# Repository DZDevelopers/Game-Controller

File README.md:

# Game Controller

This is a game controller powered by an Arduino Nano RP2040. It features two joysticks and ten buttons, designed for custom gaming and input projects.

This project is fully open-source and includes schematics, PCB design, and a simple enclosure.
### Overall game controller

### Schematic

### PCB

## Hardware Overview

Microcontroller: Arduino Micro RP2040

Buttons: Push Button Switch

joysticks: COM-09032

## Bill of Materials (BOM)

1 x Raspberry Pi Pico

10 x Push Button Switch

2 x COM-09032

1 × Custom-designed PCB

1 × Case (3D-printed)

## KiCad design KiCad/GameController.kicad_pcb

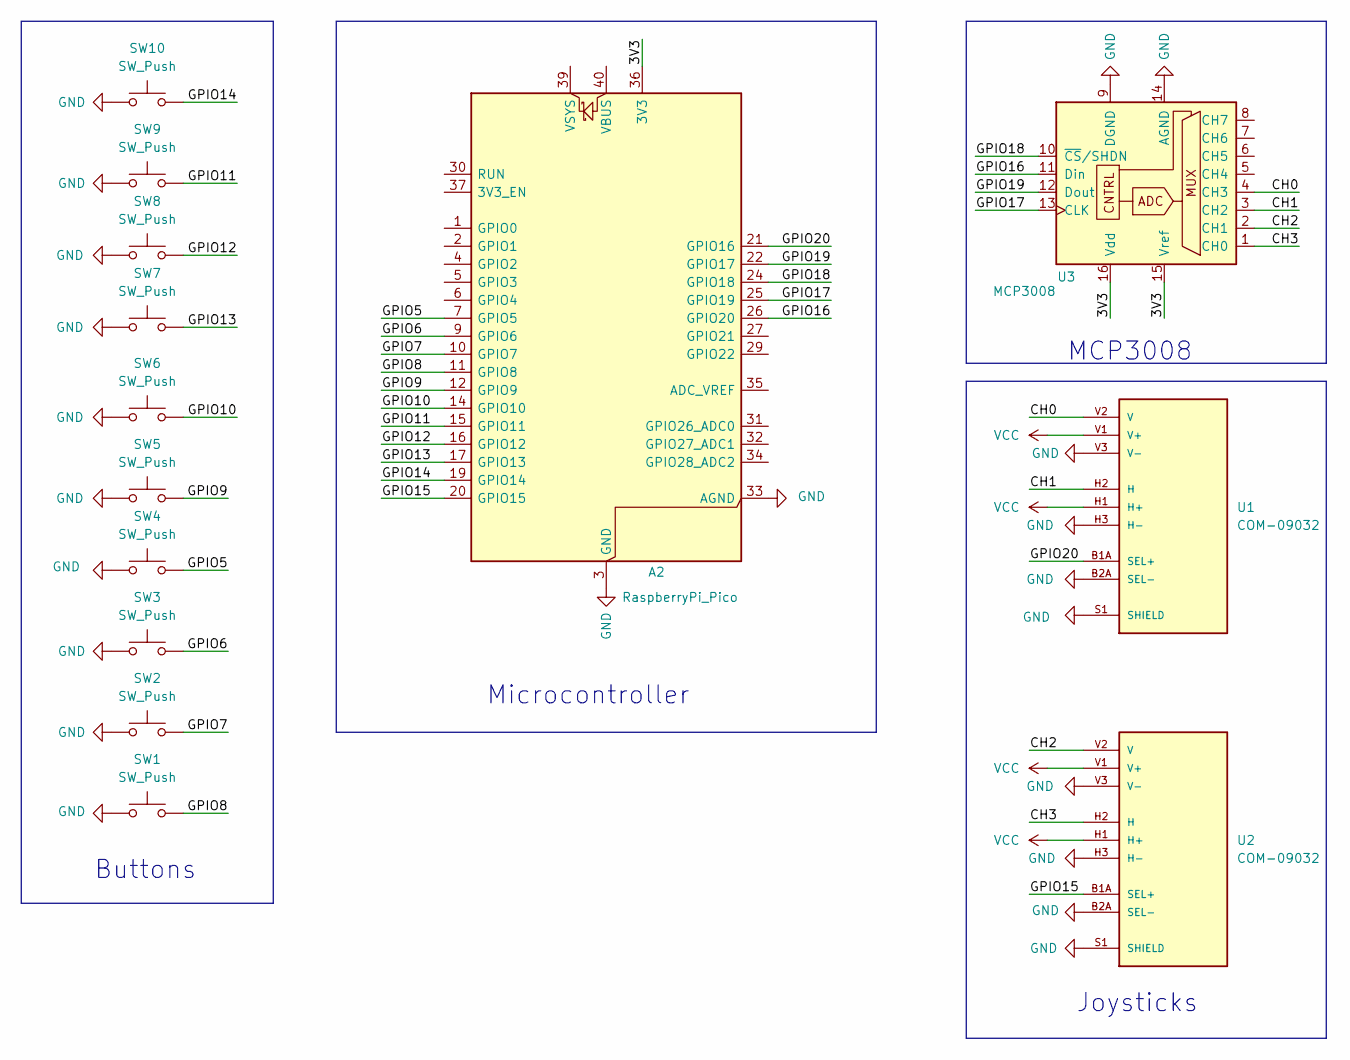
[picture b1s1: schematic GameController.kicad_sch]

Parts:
A2: RaspberryPi_Pico; RaspberryPi_Pico_Common_THT
SW1, SW2, SW3, SW4, SW5, SW6, SW7, SW8, SW9, SW10: SW_Push; SW_PUSH_6mm
U1, U2: COM-09032; XDCR_COM-09032; PARTREV N/A
U3: MCP3008; DIP-16_W7.62mm

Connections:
/3V3: A2.36 (3V3), U3.15 (Vref), U3.16 (Vdd)
/CH0: U1.V2 (V), U3.4 (CH3)
/CH1: U1.H2 (H), U3.3 (CH2)
/CH2: U2.V2 (V), U3.2 (CH1)
/CH3: U2.H2 (H), U3.1 (CH0)
/GPIO5: A2.7 (GPIO5), SW4.2
/GPIO6: A2.9 (GPIO6), SW3.2
/GPIO7: A2.10 (GPIO7), SW2.2
/GPIO8: A2.11 (GPIO8), SW1.2
/GPIO9: A2.12 (GPIO9), SW5.2
/GPIO10: A2.14 (GPIO10), SW6.2
/GPIO11: A2.15 (GPIO11), SW9.2
/GPIO12: A2.16 (GPIO12), SW8.2
/GPIO13: A2.17 (GPIO13), SW7.2
/GPIO14: A2.19 (GPIO14), SW10.2
/GPIO15: A2.20 (GPIO15), U2.B1A (SEL+)
/GPIO16: A2.26 (GPIO20), U3.11 (Din)
/GPIO17: A2.25 (GPIO19), U3.13 (CLK)
/GPIO18: A2.24 (GPIO18), U3.10 (~CS/SHDN)
/GPIO19: A2.22 (GPIO17), U3.12 (Dout)
/GPIO20: A2.21 (GPIO16), U1.B1A (SEL+)
GND: A2.3 (GND), A2.8 (GND), A2.13 (GND), A2.18 (GND), A2.23 (GND), A2.28 (GND), A2.33 (AGND), A2.38 (GND), SW1.1, SW2.1, SW3.1, SW4.1, SW5.1, SW6.1, SW7.1, SW8.1, SW9.1, SW10.1, U1.B2A (SEL-), U1.H3 (H-), U1.S1 (SHIELD), U1.S2 (SHIELD), U1.S3 (SHIELD), U1.S4 (SHIELD), U1.V3 (V-), U2.B2A (SEL-), U2.H3 (H-), U2.S1 (SHIELD), U2.S2 (SHIELD), U2.S3 (SHIELD), U2.S4 (SHIELD), U2.V3 (V-), U3.9 (DGND), U3.14 (AGND)
VCC: U1.H1 (H+), U1.V1 (V+), U2.H1 (H+), U2.V1 (V+)

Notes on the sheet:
Microcontroller
Buttons
MCP3008
Joysticks

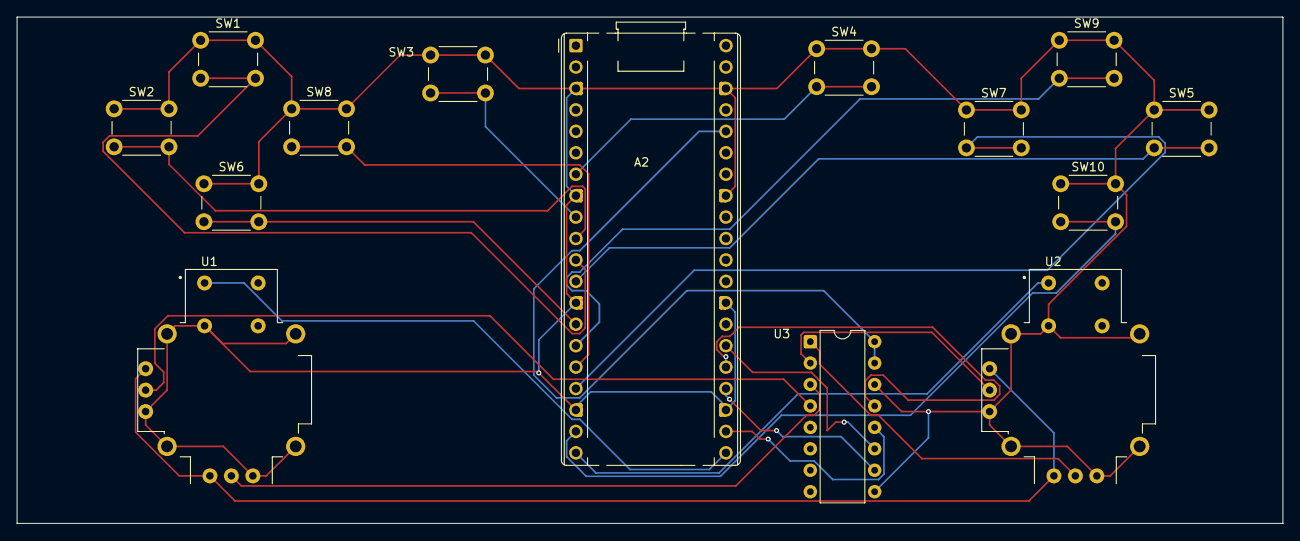
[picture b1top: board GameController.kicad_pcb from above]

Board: 2 copper layers, 150.0 x 60.0 mm, 14 parts (0 on the bottom side), 23 nets.

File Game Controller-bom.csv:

Name,Purpose,Quantity,Total Cost (USD),Link,Distributor
"solder flux","Its flex it helps solder stick to stuff",1,4.00,"https://ar.aliexpress.com/item/1005008459768970.html?spm=a2g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","Aliexpress"
"Thumbsticks","It's so the control will actualy be useable",1,2.50,"https://www.temu.com/goods.html?_bg_fs=1&goods_id=6011024854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","Temu"
"Solder Wick","To absorb solder",1,2.00,"https://www.temu.com/goods.html?_bg_fs=1&goods_id=6010995497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","Temu"
"Soldering Iron Tip","All my tips got oxidized and aren't conducting heat anymore",1,4.00,"https://www.temu.com/dz-en/10pcs--t-i-type-pure-copper-solde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","Temu"
"MCP3008","the pico pi doesnt have enough adc",1,2.75,"https://ar.aliexpress.com/item/1005006649507949.html?spm=a2g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","Aliexpress"
"Custom-designed PCB","",1,1.00,"","aivon"
"Push Button Switch","",10,2.25,"https://www.temu.com/dz-en/50pcs-6-6-5mm-tactile--pin-push-b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","Temu"
"COM-09032","",2,5.50,"https://www.temu.com/dz-en/2-pieces-for-ps3-ps4--360-one-gam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","Temu"
"Raspberry Pi Pico","",1,5.50,"https://www.temu.com/dz-en/-pico-development-board---264kb-a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","Temu"
"3D Printed Case","",1,5.00,"",""

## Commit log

2026-02-10 Stuff
2026-02-10 TUFF
2026-03-26 Update Arduino model in README description
2026-03-26 Update README with component list and pricing
    Added a table of components with quantities and prices.
2026-03-26 Replace spreadsheet link in README
    Updated link to the spreadsheet with item details.
2026-03-26 Remove link to spreadsheet from README
